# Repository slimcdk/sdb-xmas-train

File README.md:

# Stjær Dagli'Brugsens juletog

### Normalize audio
```bash
$ pip3 install ffmpeg-normalize
$ cd audio
audio$ ffmpeg-normalize -fp -pr --audio-codec libmp3lame -ext mp3 **/*.mp3 --output-folder normalized
```

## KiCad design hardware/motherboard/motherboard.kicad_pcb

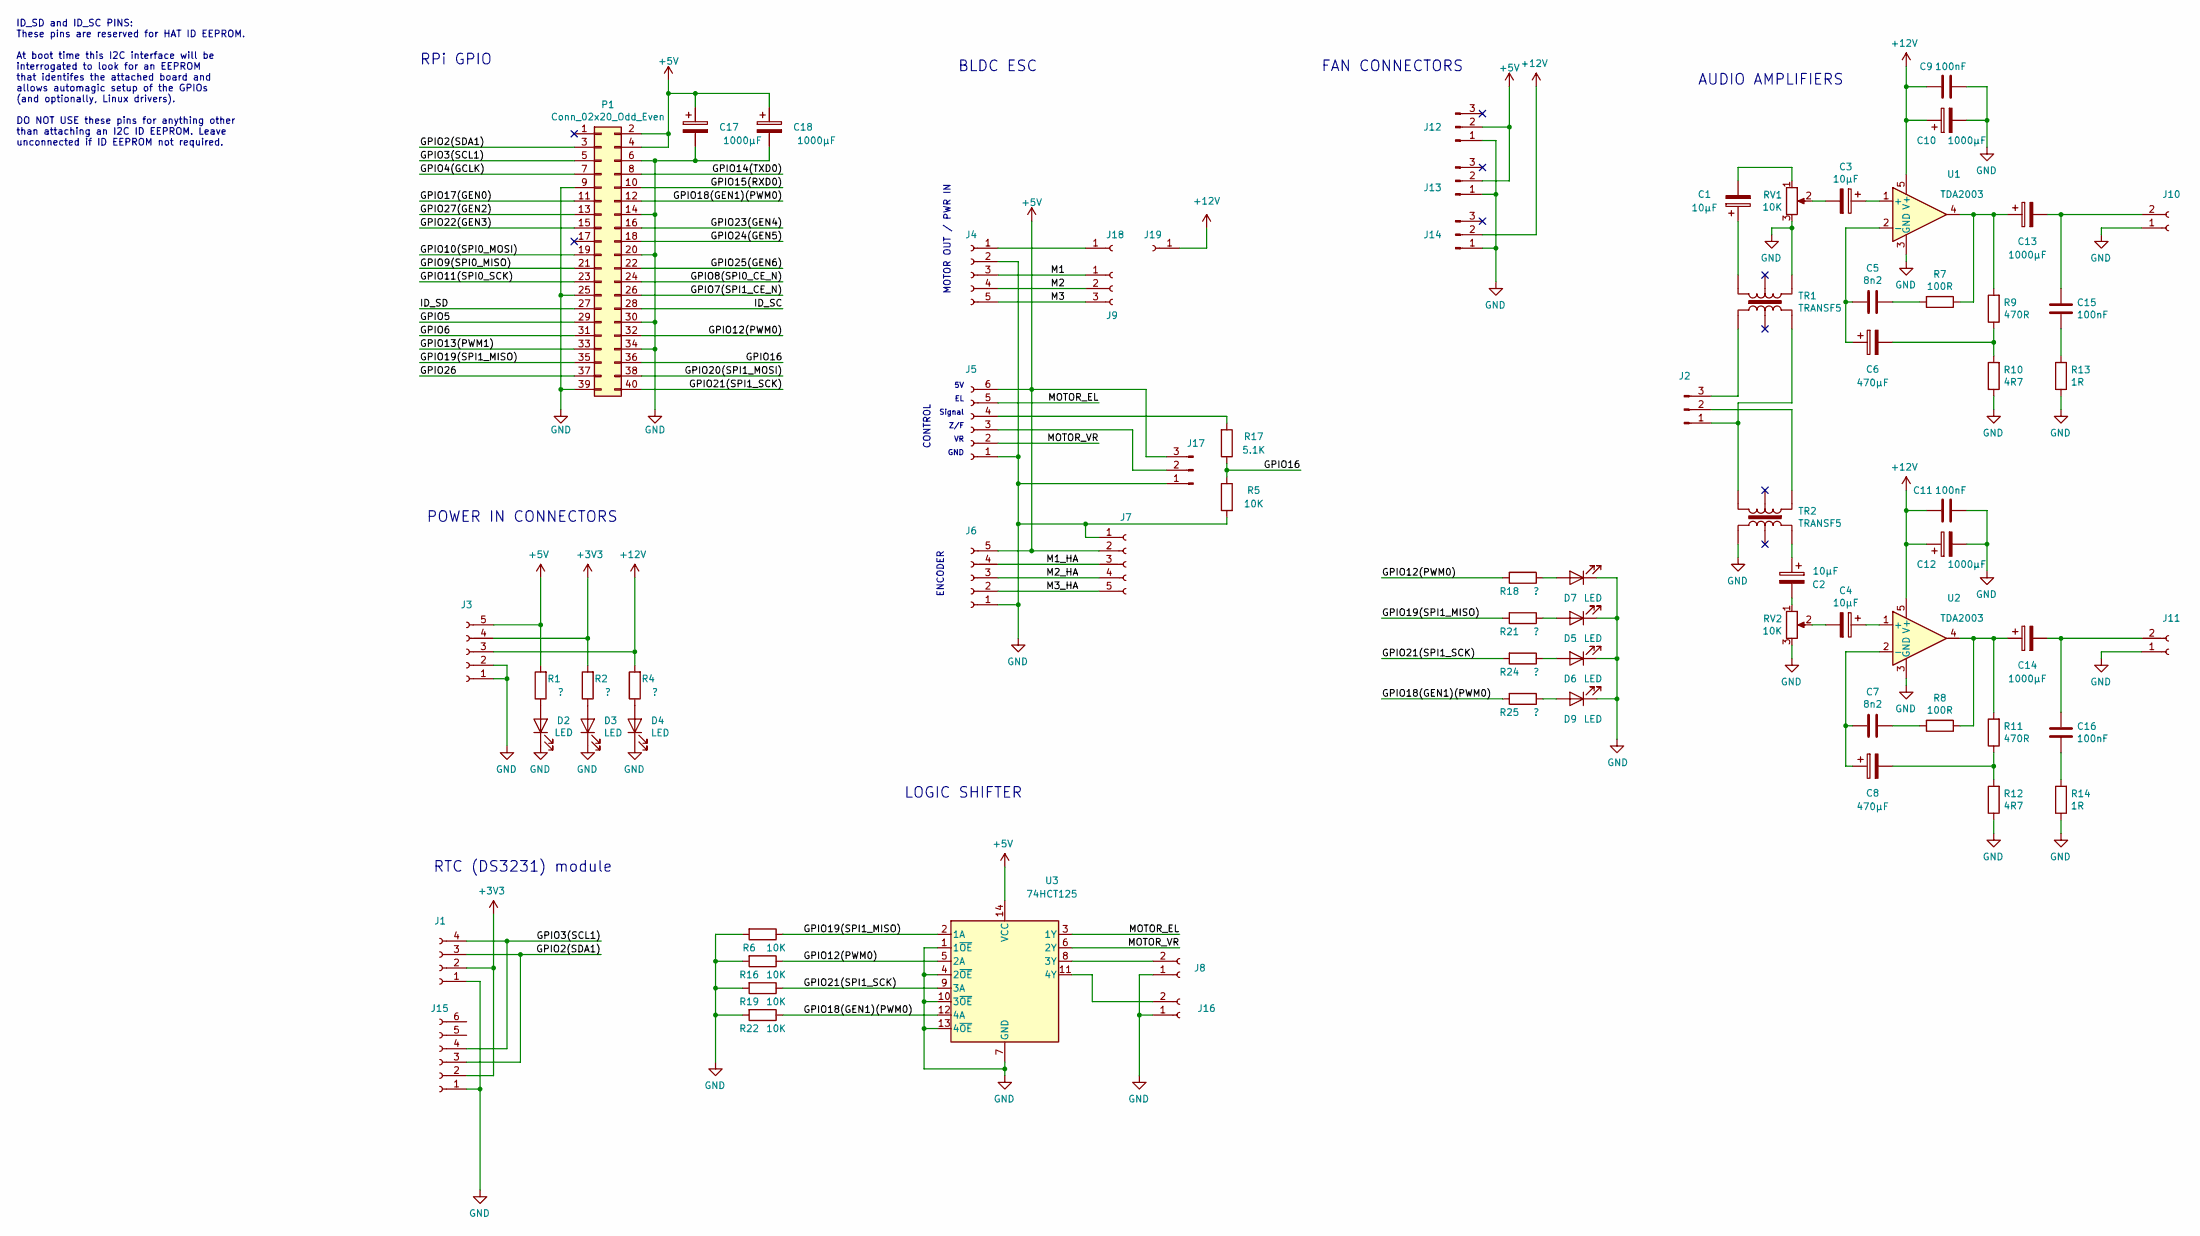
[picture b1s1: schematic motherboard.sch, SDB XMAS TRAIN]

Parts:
C1, C2, C3, C4: 10µF; CP_Radial_D6.3mm_P2.50mm
C5, C7: 8n2; C_Disc_D5.0mm_W2.5mm_P5.00mm
C6, C8: 470µF; CP_Radial_D10.0mm_P5.00mm
C9, C11, C15, C16: 100nF; C_Disc_D5.0mm_W2.5mm_P5.00mm
C10, C12, C13, C14: 1000µF; CP_Radial_D10.0mm_P5.00mm
C17, C18: 1000µF; CP_Radial_D5.0mm_P2.50mm
D2, D3, D4, D5, D6, D7, D9: LED; LED_1210_3225Metric_Pad1.42x2.65mm_HandSolder
J1: Conn_01x04_Female; PinSocket_1x04_P2.54mm_Vertical
J2, J17: Conn_01x03_Male; PinHeader_1x03_P2.54mm_Vertical
J3: Conn_01x05_Female; TerminalBlock_bornier-5_P5.08mm
J4: Conn_01x05_Female; TE_826576-5_1x05_P3.96mm_Vertical
J5, J15: Conn_01x06_Female; PinSocket_1x06_P2.54mm_Vertical
J6, J7: Conn_01x05_Female; PinSocket_1x05_P2.54mm_Vertical
J8, J10, J11, J16: Conn_01x02_Female; TerminalBlock_bornier-2_P5.08mm
J9: Conn_01x03_Female; TerminalBlock_bornier-3_P5.08mm
J12, J13, J14: Conn_01x03_Male; FanPinHeader_1x03_P2.54mm_Vertical
J18, J19: Conn_01x01_Female; SolderWirePad_1x01_Drill2.5mm
P1: Conn_02x20_Odd_Even; PinSocket_2x20_P2.54mm_Vertical
R1, R2, R4, R18, R21, R24, R25: ?; R_1210_3225Metric_Pad1.42x2.65mm_HandSolder
R5, R6, R16, R19, R22: 10K; R_1210_3225Metric_Pad1.42x2.65mm_HandSolder
R7, R8: 100R; R_1210_3225Metric_Pad1.42x2.65mm_HandSolder
R9, R11: 470R; R_1210_3225Metric_Pad1.42x2.65mm_HandSolder
R10, R12: 4R7; R_1210_3225Metric_Pad1.42x2.65mm_HandSolder
R13, R14: 1R; R_1210_3225Metric_Pad1.42x2.65mm_HandSolder
R17: 5.1K; R_1210_3225Metric_Pad1.42x2.65mm_HandSolder
RV1, RV2: 10K; Potentiometer_Bourns_3314J_Vertical
TR1, TR2: TRANSF5; MURATA_DA10XJ_Audo_Transformer
U1, U2: TDA2003; TO-220-5_P3.4x3.7mm_StaggerOdd_Lead3.8mm_Vertical
U3: 74HCT125; DIP-14_W7.62mm_Socket_LongPads

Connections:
+3V3: J1.2, J3.4, J15.2, R2.2
+5V: C17.1, C18.1, J3.5, J5.6, J6.5, J7.2, J12.2, J13.2, J17.3, P1.2, P1.4, R1.2, U3.14 (VCC)
+12V: C9.2, C10.1, C11.2, C12.1, J3.3, J14.2, J19.1, R4.2, U1.5 (V+), U2.5 (V+)
/GPIO2(SDA1): J1.3, J15.3, P1.3
/GPIO3(SCL1): J1.4, J15.4, P1.5
/GPIO4(GCLK): P1.7
/GPIO5: P1.29
/GPIO6: P1.31
/GPIO7(SPI1_CE_N): P1.26
/GPIO8(SPI0_CE_N): P1.24
/GPIO9(SPI0_MISO): P1.21
/GPIO10(SPI0_MOSI): P1.19
/GPIO11(SPI0_SCK): P1.23
/GPIO12(PWM0): P1.32, R16.1, R18.2, U3.5 (2A)
/GPIO13(PWM1): P1.33
/GPIO14(TXD0): P1.8
/GPIO15(RXD0): P1.10
/GPIO16: P1.36, R5.1, R17.1
/GPIO17(GEN0): P1.11
/GPIO18(GEN1)(PWM0): P1.12, R22.1, R25.2, U3.12 (4A)
/GPIO19(SPI1_MISO): P1.35, R6.1, R21.2, U3.2 (1A)
/GPIO20(SPI1_MOSI): P1.38
/GPIO21(SPI1_SCK): P1.40, R19.1, R24.2, U3.9 (3A)
/GPIO22(GEN3): P1.15
/GPIO23(GEN4): P1.16
/GPIO24(GEN5): P1.18
/GPIO25(GEN6): P1.22
/GPIO26: P1.37
/GPIO27(GEN2): P1.13
/ID_SC: P1.28
/ID_SD: P1.27
/M1: J4.3, J9.1
/M1_HA: J6.4, J7.3
/M2: J4.4, J9.2
/M2_HA: J6.3, J7.4
/M3: J4.5, J9.3
/M3_HA: J6.2, J7.5
/MOTOR_EL: J5.5, U3.3 (1Y)
/MOTOR_VR: J5.2, U3.6 (2Y)
GND: C9.1, C10.2, C11.1, C12.2, C17.2, C18.2, D2.1 (K), D3.1 (K), D4.1 (K), D5.1 (K), D6.1 (K), D7.1 (K), D9.1 (K), J1.1, J3.1, J3.2, J4.2, J5.1, J6.1, J7.1, J8.1, J10.1, J11.1, J12.1, J13.1, J14.1, J15.1, J16.1, J17.1, P1.6, P1.9, P1.14, P1.20, P1.25, P1.30, P1.34, P1.39, R5.2, R6.2, R10.1, R12.1, R13.1, R14.1, R16.2, R19.2, R22.2, RV1.3, RV2.3, TR1.4, TR2.4, U1.3 (GND), U2.3 (GND), U3.1 (1~OE), U3.4 (2~OE), U3.7 (GND), U3.10 (3~OE), U3.13 (4~OE)
unnamed: C1.1, TR1.6
unnamed: C1.2, RV1.1
unnamed: C2.1, TR2.6
unnamed: C2.2, RV2.1
unnamed: C3.1, U1.1 (+)
unnamed: C3.2, RV1.2
unnamed: C4.1, U2.1 (+)
unnamed: C4.2, RV2.2
unnamed: C5.1, R7.2
unnamed: C5.2, C6.1, U1.2 (-)
unnamed: C6.2, R9.1, R10.2
unnamed: C7.1, R8.2
unnamed: C7.2, C8.1, U2.2 (-)
unnamed: C8.2, R11.1, R12.2
unnamed: C13.1, R7.1, R9.2, U1.4
unnamed: C13.2, C15.1, J10.2
unnamed: C14.1, R8.1, R11.2, U2.4
unnamed: C14.2, C16.1, J11.2
unnamed: C15.2, R13.2
unnamed: C16.2, R14.2
unnamed: D2.2 (A), R1.1
unnamed: D3.2 (A), R2.1
unnamed: D4.2 (A), R4.1
unnamed: D5.2 (A), R21.1
unnamed: D6.2 (A), R24.1
unnamed: D7.2 (A), R18.1
unnamed: D9.2 (A), R25.1
unnamed: J2.1, TR1.3, TR2.3
unnamed: J2.2, TR2.1
unnamed: J2.3, TR1.1
unnamed: J5.4, R17.2
unnamed: J8.2, U3.8 (3Y)
unnamed: J16.2, U3.11 (4Y)
unnamed: J5.3, J17.2
unnamed: J4.1, J18.1

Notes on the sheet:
RPi GPIO
RTC (DS3231) module
BLDC ESC
POWER IN CONNECTORS
ID_SD and ID_SC PINS: These pins are reserved for HAT ID EEPROM. At boot time this I2C interface will be interrogated to look for an EEPROM that identifes the attached board and allows automagic setup of the GPIOs (and optionally, Linux drivers). DO NOT USE these pins for anything other than attach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
AUDIO AMPLIFIERS
FAN CONNECTORS
LOGIC SHIFTER
CONTROL
MOTOR OUT / PWR IN
Signal
Z/F
GND
ENCODER

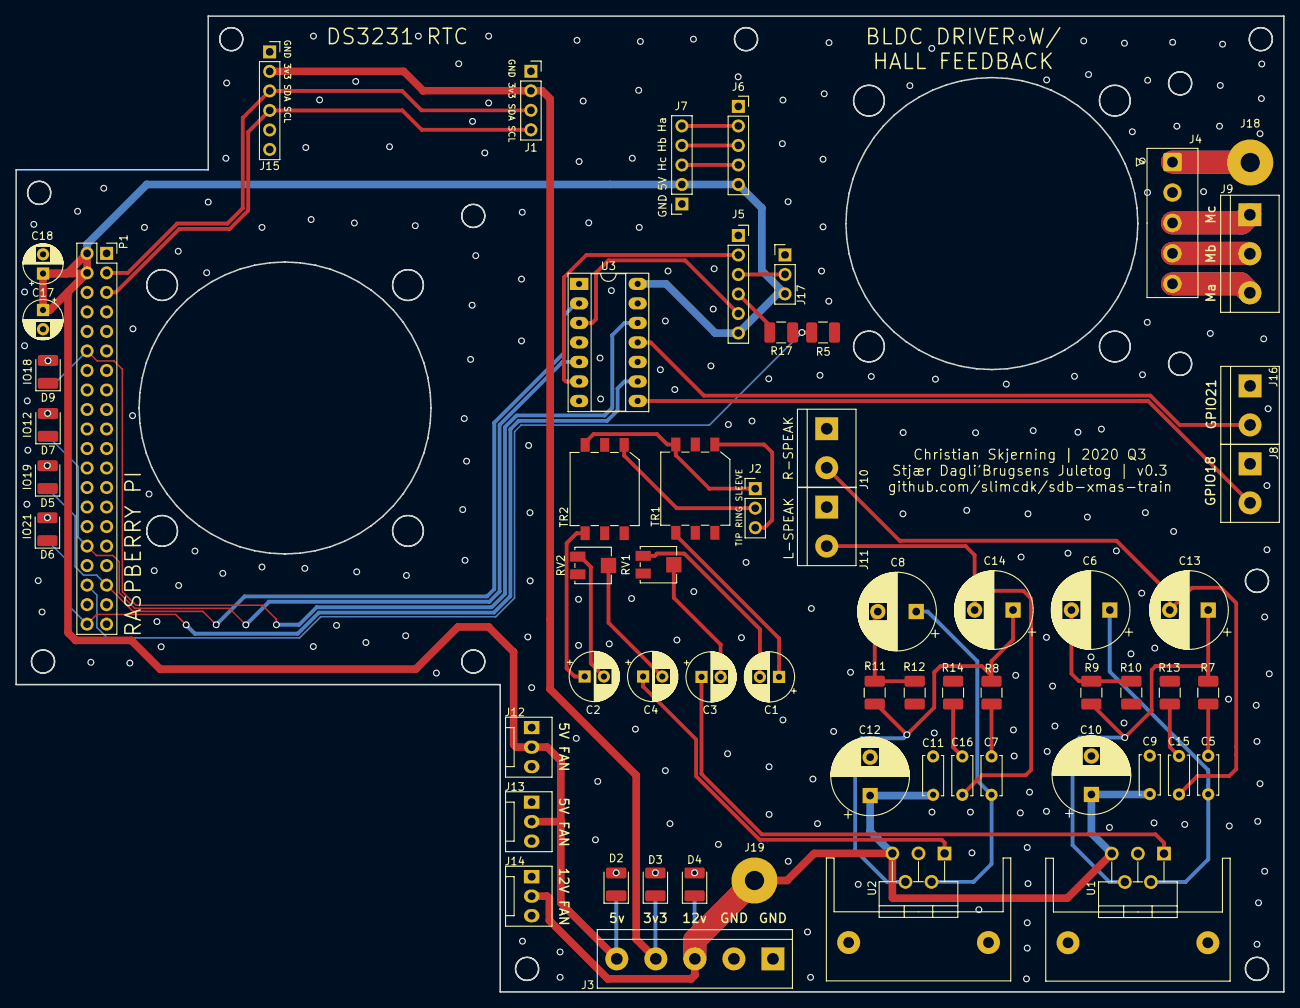
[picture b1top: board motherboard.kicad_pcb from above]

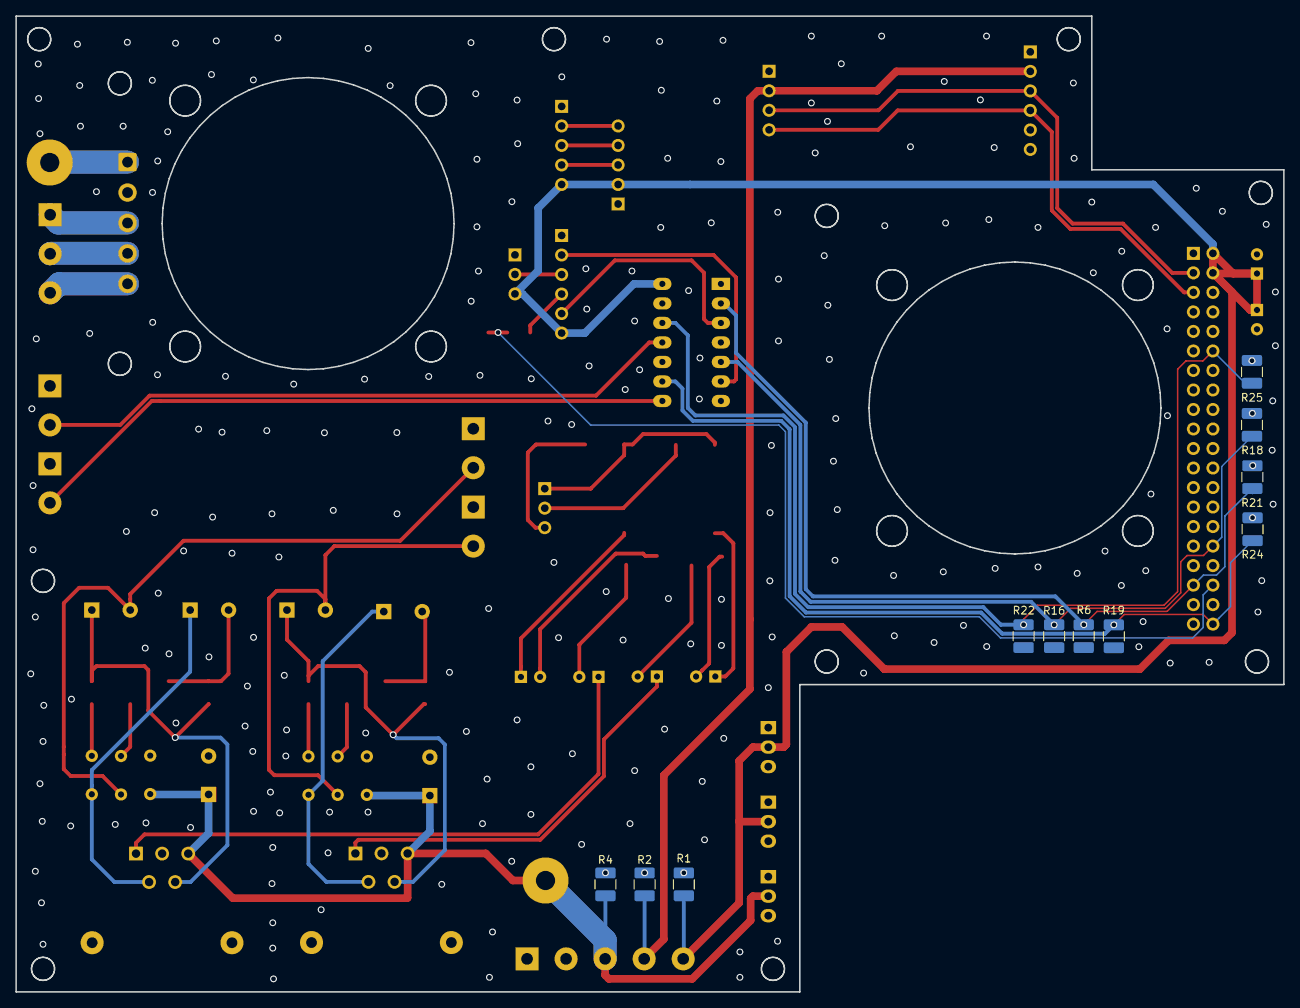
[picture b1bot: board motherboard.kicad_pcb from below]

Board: 2 copper layers, 165.0 x 127.0 mm, 73 parts (11 on the bottom side), 54 nets.

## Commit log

2019-10-21 rpi omxplayer test
2019-10-28 firmware
2019-11-02 electronic mounting
2019-11-02 untrack .vscode and firmware update
2019-11-03 simpler logic
2019-11-03 structs
2019-11-05 auto play working
2019-11-06 docker compose
2019-11-06 auto start from reboot
2019-11-06 adjustments
2019-11-07 adjusting; new firm/software
2019-11-12 speed graphs
2019-11-12 refractored speed_graph()
2019-11-13 working conductor
2019-11-14 conductor finished
2019-11-14 docker
2019-11-15 docker script
2019-11-16 first test
2019-11-16 hardware; speed graph
2019-11-17 almost donw
2019-11-18 sd card migration
2019-11-19 try except; print format; timezone in Docker
2019-11-24 ready
2019-11-24 ready..
2019-11-25 hardware mount
2019-11-26 conductor done; music normalizer added
2019-11-26 ready for delivery
2019-11-26 simpler playlist visuals
2019-11-26 cleaned up repo
2019-11-26 clear playlist
2019-11-27 FINISHED!
2019-11-27 flipped opening hours..
2020-01-06 schematic for motherboard
2020-01-07 time change
2020-01-07 PCB motherboard
2020-10-15 balena deploy
2020-10-16 new hardware and refactored directories
2020-10-16 imported pcb
2020-10-17 getting hardware rtc to work
2020-10-17 started on go application
2020-10-18 music vault and rtc
2020-10-18 new go mod structure
2020-10-19 work on hardware motherboard
2020-10-20 work on software
2020-10-23 layout of first mb; test print
2020-10-23 software structure
2020-10-23 ordered first version
2020-10-25 better deployment
2020-10-30 added lights to schematic
2020-10-30 go-rpio not working in docker
2020-10-30 python codebase
2020-11-02 pcb design v2
2020-11-02 pcb plots
2020-11-02 exposed another GPIO
2020-11-03 gerber files for pcb revision 0.2
2020-11-06 conductor build
2020-11-07 testing balena gpio
2020-11-07 additional gpio
2020-11-07 pcb-mount
2020-11-07 working gpio and audio tests
2020-11-07 other src structure
2020-11-07 gitignore music fix
2020-11-08 mostly working business logic
2020-11-08 removed old hardware files
2020-11-10 version v0.3
2020-11-10 multistage build
2020-11-10 keep main lights on until show has finished
2020-11-10 audio gain normalizing
2020-11-10 adjusted heatsink
2020-11-12 hardware revision 0.3
2020-11-12 refactored a little
2020-11-19 hardware v0.3
2020-11-22 ready for 2nd year
2025-12-05 Bump github.com/sirupsen/logrus from 1.7.0 to 1.8.3 in /src/.go-src
    Bumps [github.com/sirupsen/logrus](https://github.com/sirupsen/logrus) from 1.7.0 to 1.8.3.
    - [Release notes](https://github.com/sirupsen/logrus/releases)
    - [Changelog](https://github.com/sirupsen/logrus/blob/master/CHANGELOG.md)
    - [Commits](https://github.com/sirupsen/logrus/compare/v1.7.0...v1.8.3)
    ---
    updated-dependencies:
